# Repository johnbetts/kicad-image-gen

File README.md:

# kicad-image-gen

Generate PNG screenshots of KiCad PCBs that look like the PCB editor -- headlessly, from the command line or Python.

## Why This Exists

I was designing PCBs with an AI-assisted workflow ([kicad-ai-workflow](https://github.com/johnbetts/kicad-ai-workflow)) and hit a wall: every time I wanted Claude to review a board layout, I had to manually screenshot the KiCad PCB editor and paste the image into the conversation. Over and over. For every iteration.

I tried `kicad-cli` exports, but the raw SVG/PDF output looked nothing like the editor -- wrong colors, no ratsnest, no pad labels, missing mounting holes. The images were useless for AI-driven layout review because they didn't show the information an EE needs to evaluate placement: which pads connect where, what's routed, what isn't.

So I built this tool. It generates images that match the KiCad PCB editor appearance -- dark navy background, red pads, cyan mounting holes, visible ratsnest lines, pad numbers and net names -- using a custom color theme, SVG post-processing, and careful layer ordering.

Now my workflow is fully automated: generate a board, render images, feed them to Claude for review, apply fixes, re-render, repeat. The whole loop runs inside [autoresearch](https://github.com/johnbetts/kicad-ai-workflow) iterations -- modify placement, render, score, keep or discard -- without ever opening KiCad.

## Requirements

- **KiCad 10** (uses `kicad-cli` under the hood)
- **Python 3.10+**
- **rsvg-convert** (for SVG-to-PNG conversion): `brew install librsvg`

## Install

```bash
pip install -e .

# Install the custom KiCad color theme (required for editor-matching colors)
cp kicad_image_gen_theme.json ~/Library/Preferences/kicad/10.0/colors/kicad_image_gen.json
```

## CLI Usage

```bash
# 2D editor-style screenshot (with ratsnest + pad labels)
kicad-image-gen 2d board.kicad_pcb -o board_2d.png

# Composite mode (3D render base + overlay -- photorealistic)
kicad-image-gen 2d --composite board.kicad_pcb -o board_composite.png

# 3D rendered view
kicad-image-gen 3d board.kicad_pcb --view iso -q high --floor -o board_3d.png

# Full set: 2D top/bottom + 3D top/bottom/iso
kicad-image-gen both board.kicad_pcb -o output_dir/
```

### 2D Options

| Flag | Description |
|------|-------------|
| `-l`, `--layers` | Layer list or preset: `all`, `top`, `bottom`, `copper`, `silkscreen`, `fab` |
| `-w`, `--width` | Output width in pixels (default: 4800) |
| `-t`, `--theme` | KiCad color theme name (default: `kicad_image_gen`) |
| `--composite` | Use 3D renderer as base with PIL overlays |
| `--no-ratsnest` | Hide ratsnest lines |
| `--no-pad-labels` | Hide pad numbers and net names |
| `--pad-labels` | Show pad numbers and net names (default) |
| `-m`, `--mirror` | Mirror the board |
| `--bw` | Black and white |

### 3D Options

| Flag | Description |
|------|-------------|
| `--view` | Preset: `top`, `bottom`, `iso`, `iso-back`, `iso-bottom`, `front`, `back`, `left`, `right` |
| `-w`, `--width` | Image width (default: 1600) |
| `--height` | Image height (default: 900) |
| `-q`, `--quality` | `basic` or `high` |
| `--perspective` | Perspective projection |
| `--floor` | Enable floor, shadows, post-processing |
| `--zoom` | Camera zoom level |
| `--rotate` | Custom rotation as `X,Y,Z` degrees |

## Python API

```python
from kicad_image_gen import render_2d, render_3d, render_2d_composite, render_all

# 2D editor view with ratsnest and pad labels
render_2d("board.kicad_pcb", "board_2d.png", width=4800)

# 2D clean (no overlays)
render_2d("board.kicad_pcb", "board_clean.png", ratsnest=False, pad_labels=False)

# 3D isometric
render_3d("board.kicad_pcb", "board_3d.png", view="iso", quality="high", floor=True)

# Composite (photorealistic base + ratsnest overlay)
render_2d_composite("board.kicad_pcb", "board_composite.png", ratsnest=True)

# Full set: 2d_top, 2d_bottom, 3d_top, 3d_bottom, 3d_iso
results = render_all("board.kicad_pcb", "output/")
```

## What It Renders

The 2D output matches the KiCad PCB editor appearance:

- **Red pads** via custom color theme with transparent soldermask
- **Cyan mounting holes** injected at NPTH pad locations
- **Ratsnest lines** (MST-based) showing unrouted net connectivity
- **Pad labels** with pin numbers (cyan) and net names scaled to pad size
- **Dark navy background** with subtle board substrate fill
- **Yellow edge cuts** for board outline visibility
- **Board margin** via viewBox padding

## Architecture

Thin wrapper around `kicad-cli` (KiCad 10's official CLI). No dependency on the deprecated `pcbnew` Python bindings.

- **2D pipeline**: `kicad-cli pcb export svg` with custom theme and layer ordering -> SVG post-processing (background, mounting holes, ratsnest, pad labels) -> `rsvg-convert` -> PNG
- **3D pipeline**: `kicad-cli pcb render` -> PNG (direct output)
- **Composite pipeline**: `kicad-cli pcb render --side top` -> Pillow overlay compositing
- **PCB parsing**: Standalone `.kicad_pcb` S-expression regex parser for pads, nets, bounds, mounting holes

## Using with AI Agents

This tool was built specifically for AI-driven PCB design loops. Other Claude Code skills can call it directly:

```python
from kicad_image_gen import render_2d
render_2d(pcb_path, output_path)
```

Or via CLI in any agent's bash:

```bash
kicad-image-gen 2d board.kicad_pcb -o placement.png
```

## License

Apache 2.0

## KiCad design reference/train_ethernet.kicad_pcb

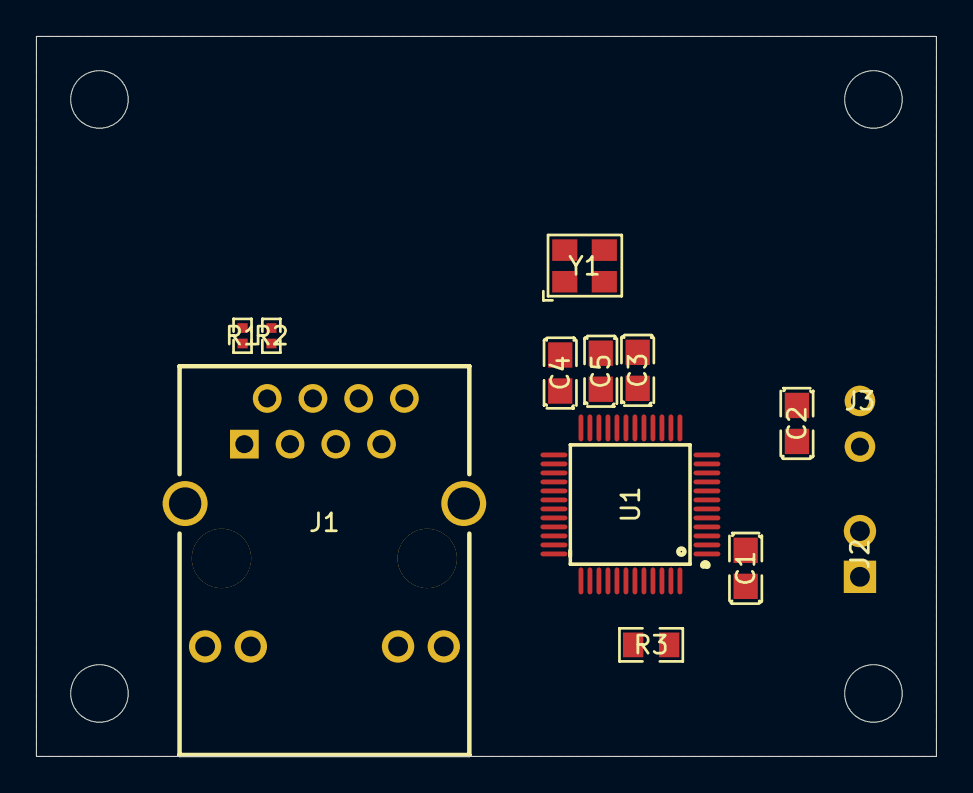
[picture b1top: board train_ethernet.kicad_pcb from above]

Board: 2 copper layers, 50.0 x 40.0 mm, 17 parts (0 on the bottom side), 13 nets, no tracks yet.

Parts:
C1, C3: 100nF; C0805
C2: 10uF; C0805
C4, C5: 22pF; C0805
H1, H2, H3, H4: MountingHole; MountingHole_2.7mm_M2.5
J1: HR911105A; RJ45-TH_HR911105A
J2: SPI_Header; HDR-TH_2P-P2.54-V-M-1
J3: PWR_Header; PinHeader_1x02_P2.54mm_Vertical
R1, R2: 49.9R; R0402
R3: 12.1K; R0805
U1: W5500; LQFP-48_L7.0-W7.0-P0.50-LS9.0-BL
Y1: 25MHz; OSC-SMD_4P-L3.2-W2.5-BL

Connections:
+3V3: C2.1, J1.9, J1.11, J3.1, U1.10, U1.15, U1.26, U1.29, U1.32, U1.35, U1.38, U1.41, U1.44, U1.47
+3V3_U1_DEC: C1.1, U1.2
AVDD_U1_DEC: C3.1, U1.22
GND: C1.2, C2.2, C3.2, C4.2, C5.2, J1.10, J1.12, J3.2, R1.2, R2.2, R3.2, U1.1, U1.11, U1.14, U1.18, U1.21, U1.25, U1.27, U1.28, U1.30, U1.31, U1.33, U1.34, U1.36, U1.37, U1.39, U1.40, U1.42, U1.43, U1.45, U1.46, U1.48
RSVD: R3.1, U1.3
RX+: J1.3, U1.19
RX-: J1.6, U1.20
SPI_MISO: J2.2, U1.5
SPI_MOSI: J2.1, U1.4
TX+: J1.1, R1.1, U1.16
TX-: J1.2, R2.1, U1.17
XTAL1: U1.23, Y1.1
XTAL2: U1.24, Y1.2

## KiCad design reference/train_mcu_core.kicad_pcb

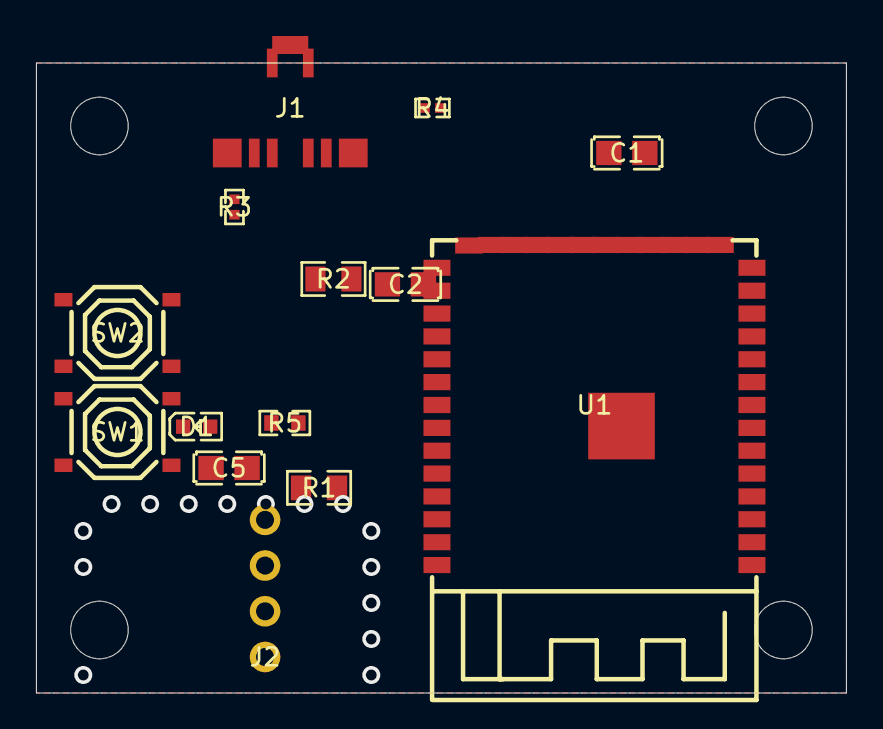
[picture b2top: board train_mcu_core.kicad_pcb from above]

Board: 2 copper layers, 45.0 x 35.0 mm, 18 parts (0 on the bottom side), 13 nets, no tracks yet.

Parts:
C1, C5: 100nF; C0805
C2: 10uF; C0805
D1: LED; LED0603-RD
H1, H2, H3, H4: MountingHole; MountingHole_2.7mm_M2.5
J1: USB-C; USB_C_Receptacle_GCT_USB4105
J2: UART_Header; PinHeader_1x04_P2.54mm
R1, R2: 10K; R0805
R3, R4: 5.1K; R0402
R5: 330R; R0603
SW1: BOOT; SW-SMD_4P-L5.1-W5.1-P3.70-LS6.5-TL_H1.5
SW2: RESET; SW-SMD_4P-L5.1-W5.1-P3.70-LS6.5-TL_H1.5
U1: ESP32-S3-WROOM-1; WIRELM-SMD_ESP32-S3-WROOM-1

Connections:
+3V3: C2.1, J2.3, R1.1, R2.1
+3V3_U1_DEC: C1.1, U1.2
BOOT: R2.2, SW1.1, U1.27
CC1: J1.A5, R3.1
CC2: J1.B5, R4.1
EN: R1.2, SW2.1, U1.3
GND: C1.2, C2.2, C5.2, D1.2, J1.A1, J1.S1, J2.4, R3.2, R4.2, SW1.2, SW2.2, U1.1, U1.40, U1.41
LED: R5.1, U1.38
LED_A: D1.1, R5.2
UART_RX: J2.2, U1.37
UART_TX: J2.1, U1.36
USB_DM: J1.A7, U1.14
USB_DP: J1.A6, U1.13

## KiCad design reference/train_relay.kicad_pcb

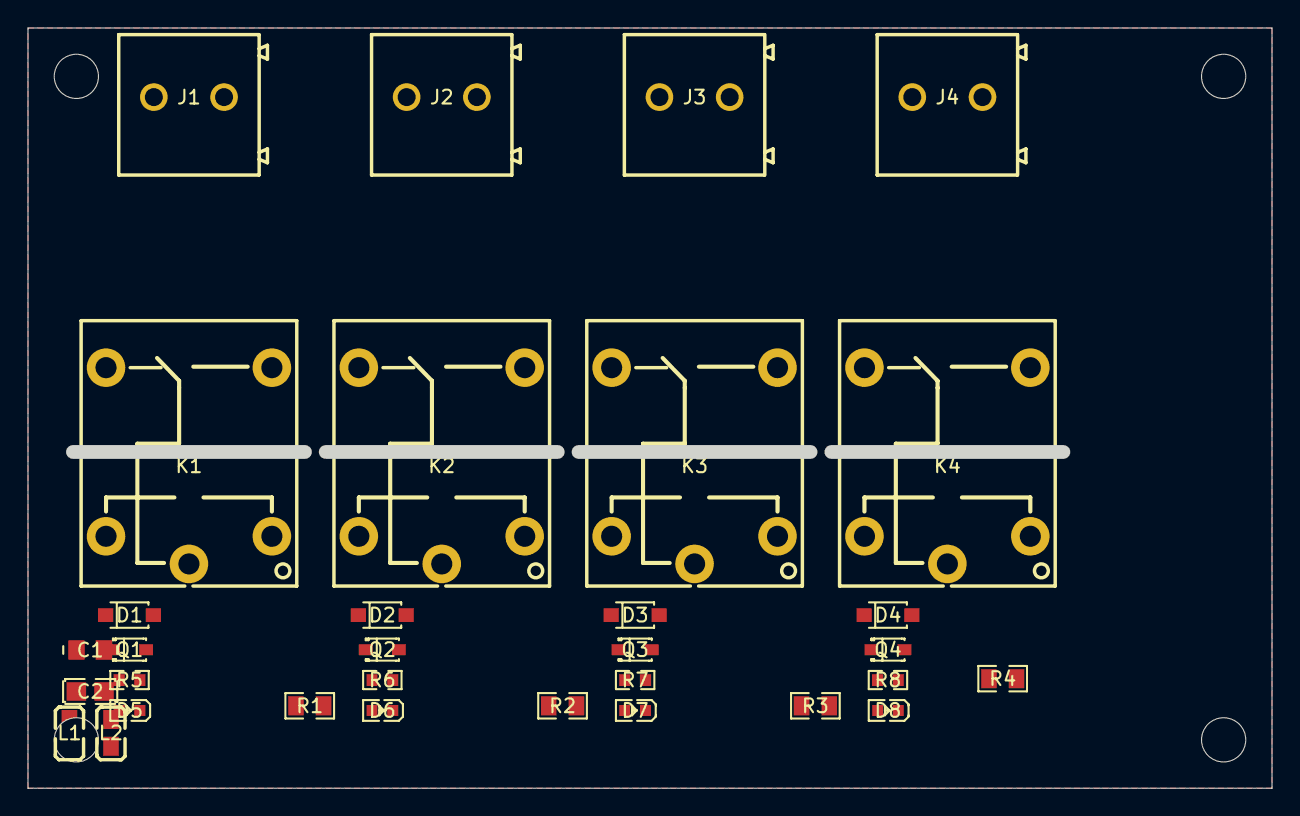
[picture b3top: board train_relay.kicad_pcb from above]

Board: 2 copper layers, 90.0 x 55.0 mm, 36 parts (0 on the bottom side), 22 nets, no tracks yet.

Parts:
C1: 100uF; C_0805_2012Metric
C2: 10uF; C0805
D1, D2, D3, D4: 1N4148; SOD-123F_L2.7-W1.6-LS3.8-RD
D5, D6, D7, D8: LED; LED0603-RD
H1, H2, H3, H4: MountingHole; MountingHole_2.7mm_M2.5
J1, J2, J3, J4: Screw_Terminal_3P; CONN-TH_2P-P5.00_WJ500V-5.08-2P
K1, K2, K3, K4: SRD-05VDC-SL-C; RELAY-TH_SRD-XXVDC-XL-C
L1, L2: 600R@100MHz; L0805
Q1, Q2, Q3, Q4: SS8050; SOD-323_L1.8-W1.3-LS2.5-FD
R1, R2, R3, R4: 1K; R0805
R5, R6, R7, R8: 330R; R0603

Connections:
+5V_RELAY: C1.1, C2.1, D1.2, D2.2, D3.2, D4.2, K1.1, K2.1, K3.1, K4.1, L1.2
GND_RELAY: C1.2, C2.2, D5.2, D6.2, D7.2, D8.2, L2.2
LED1_A: D5.1, R5.2
LED2_A: D6.1, R6.2
LED3_A: D7.1, R7.2
LED4_A: D8.1, R8.2
RELAY_COIL1: D1.1, K1.4, Q1.2, R5.1
RELAY_COIL2: D2.1, K2.4, Q2.2, R6.1
RELAY_COIL3: D3.1, K3.4, Q3.2, R7.1
RELAY_COIL4: D4.1, K4.4, Q4.2, R8.1
RELAY_COM1: J1.1, K1.5
RELAY_COM2: J2.1, K2.5
RELAY_COM3: J3.1, K3.5
RELAY_COM4: J4.1, K4.5
RELAY_DRIVE1: Q1.1, R1.2
RELAY_DRIVE2: Q2.1, R2.2
RELAY_DRIVE3: Q3.1, R3.2
RELAY_DRIVE4: Q4.1, R4.2
RELAY_NO1: J1.2, K1.3
RELAY_NO2: J2.2, K2.3
RELAY_NO3: J3.2, K3.3
RELAY_NO4: J4.2, K4.3

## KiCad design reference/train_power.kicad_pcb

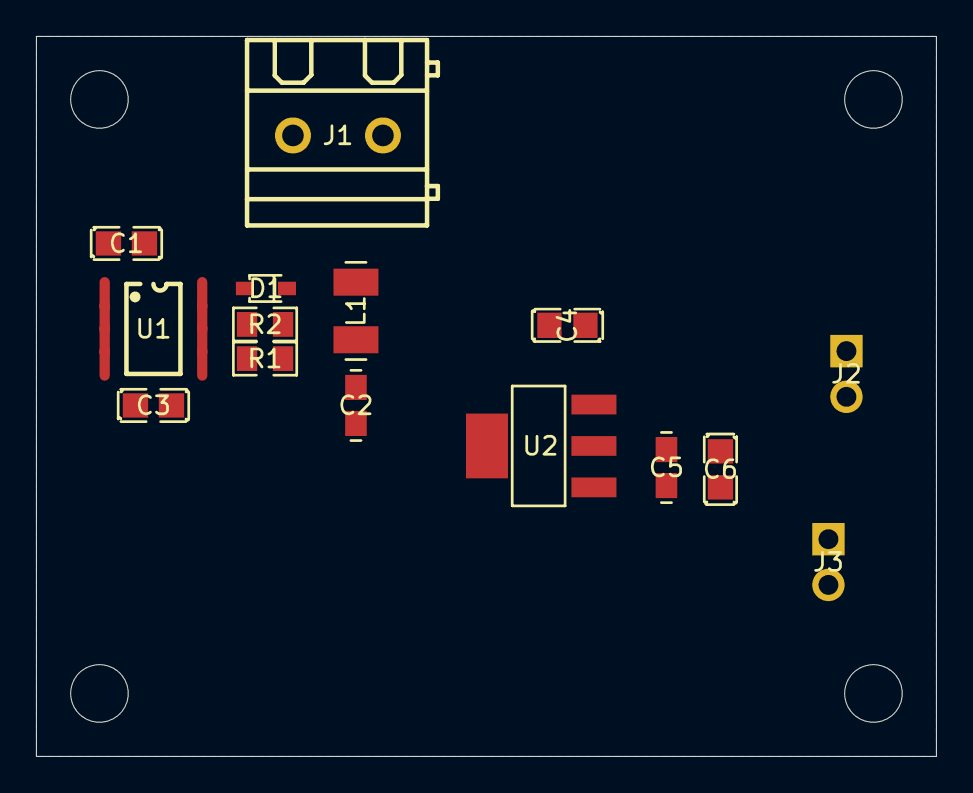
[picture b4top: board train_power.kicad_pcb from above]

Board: 2 copper layers, 50.0 x 40.0 mm, 19 parts (0 on the bottom side), 9 nets, no tracks yet.

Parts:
C1, C4: 10uF; C0805
C2, C5: 22uF; C_0805_2012Metric
C3, C6: 100nF; C0805
D1: SS14; SOD-323_L1.8-W1.3-LS2.5-RD
H1, H2, H3, H4: MountingHole; MountingHole_2.7mm_M2.5
J1: Screw_Terminal_2P; CONN-TH_2P-P5.00_WJ128V-5.0-2P
J2, J3: Pin_Header_2P; HDR-TH_2P-P2.54-V-M-1
L1: 10uH; L_1210
R1: 100K; R0805
R2: 33K; R0805
U1: TPS54331; SOIC-8_L5.0-W4.0-P1.27-LS6.0-BL
U2: AMS1117-3.3; SOT-223-3_L6.5-W3.4-P2.30-LS7.0-BR

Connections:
+3V3_C5_DEC: C5.1, C6.1, J3.1, U2.2, U2.4
+5V: J2.1, R1.1
+5V_C2_DEC: C2.1, L1.2
+5V_C4_DEC: C4.1, U2.3
+24V: C1.1, J1.2, U1.2, U1.3
BST_U1: C3.1, U1.1
FB: R1.2, R2.1, U1.5
GND: C1.2, C2.2, C4.2, C5.2, C6.2, D1.1, J1.1, J2.2, J3.2, R2.2, U1.6, U1.8, U2.1
SW: C3.2, D1.2, L1.1, U1.7

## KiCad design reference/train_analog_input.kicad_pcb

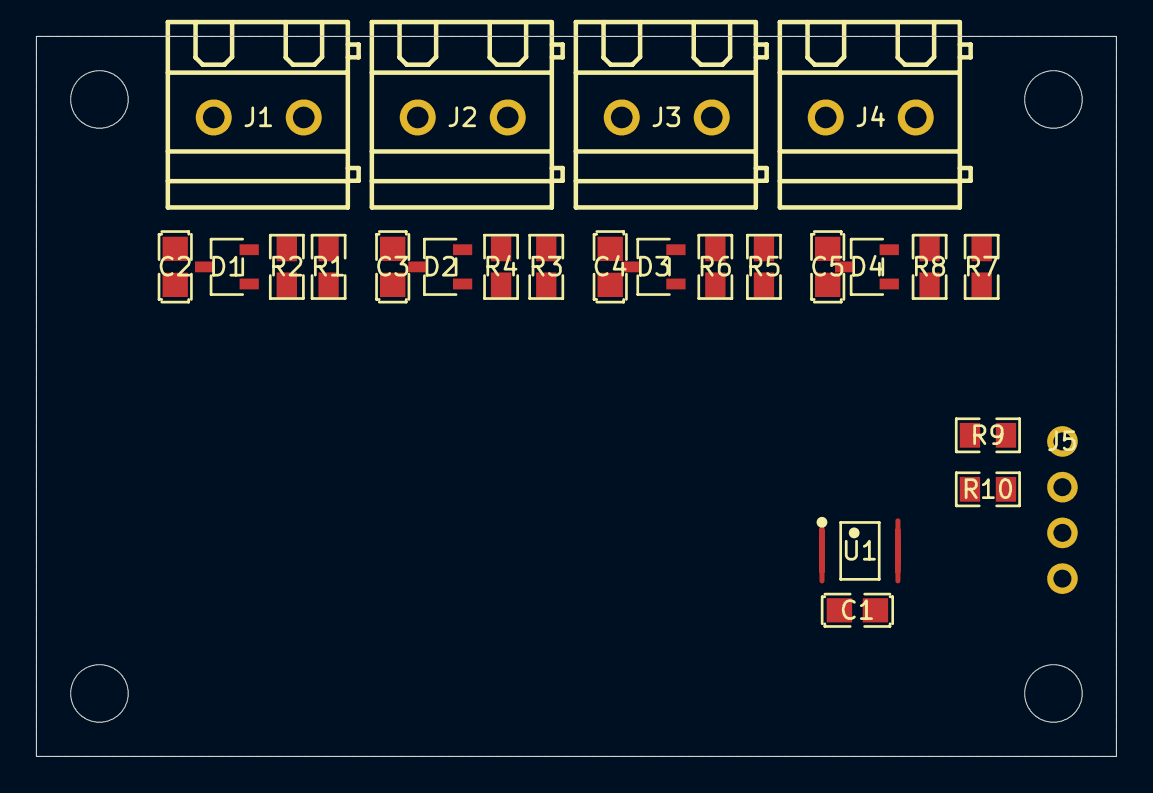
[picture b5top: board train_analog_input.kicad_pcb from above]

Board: 2 copper layers, 60.0 x 40.0 mm, 29 parts (0 on the bottom side), 17 nets, no tracks yet.

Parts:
C1, C2, C3, C4, C5: 100nF; C0805
D1, D2, D3, D4: PESD3V3; SOT-23-3_L2.9-W1.6-P1.90-LS2.8-BR
H1, H2, H3, H4: MountingHole; MountingHole_2.7mm_M2.5
J1, J2, J3, J4: Screw_Terminal_2P; CONN-TH_2P-P5.00_WJ128V-5.0-2P
J5: PinHeader_1x04
R1, R2, R3, R4, R5, R6, R7, R8: 10K; R0805
R9, R10: 4.7K; R0805
U1: ADS1115; MSOP-10_L3.0-W3.0-P0.50-LS5.0-BL

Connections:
+3V3: J5.3, R9.1, R10.1
+3V3_U1_DEC: C1.1, U1.8
AIN1_DIV: R1.2, R2.1
AIN1_PROT: C2.1, D1.1, U1.5
AIN1_RAW: J1.1, R1.1
AIN2_DIV: R3.2, R4.1
AIN2_PROT: C3.1, D2.1, U1.4
AIN2_RAW: J2.1, R3.1
AIN3_DIV: R5.2, R6.1
AIN3_PROT: C4.1, D3.1, U1.6
AIN3_RAW: J3.1, R5.1
AIN4_DIV: R7.2, R8.1
AIN4_PROT: C5.1, D4.1, U1.7
AIN4_RAW: J4.1, R7.1
GND: C1.2, C2.2, C3.2, C4.2, C5.2, D1.2, D2.2, D3.2, D4.2, J1.2, J2.2, J3.2, J4.2, J5.4, R2.2, R4.2, R6.2, R8.2, U1.1, U1.3
SCL: J5.2, R10.2, U1.10
SDA: J5.1, R9.2, U1.9
